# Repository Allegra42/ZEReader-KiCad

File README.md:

<!-- # ZEReader-PCB
ZEReader-PCB is a custom hardware design, intended to be used with the [ZEReader firmware](https://github.com/Allegra42/ZEReader).  
The project is supported by [AISLER](https://aisler.net/en?utm_source=zereader), which sponsor prototying PCBs. See [Production](#production) for more information.  
Thanks [AISLER](https://aisler.net/en?utm_source=zereader)!

- [ZEReader-PCB](#zereader-pcb)
  - [PCB Revisions](#pcb-revisions)
    - [Revision 2](#revision-2)
      - [Known Issues Rev 2](#known-issues-rev-2)
    - [Revision 1](#revision-1)
      - [Known Issues Rev 1](#known-issues-rev-1)
  - [CI and Automation](#ci-and-automation)
  - [Production](#production)
  - [License](#license)

## PCB Revisions
### Revision 2

ZEReader revision 2 is a major redesign of the PCB.
Major improvements and changes in rev 2:
- connected USB-C datalines and added additional ESD and overvoltage protection with USB optimized ESD diodes and a polyfuse
- switched to BQ25170 as a charging controller
- removed the on-PCB NTC for monitoring the lipo temperature in favor for an integrated one
- implemented a new button-based on/off mechanism [based on a self-holding circuit](https://marx.engineer/blog/a-gentle-power-off/)
- fixed FFC connector inversion from rev 1
- removed switch in the display's booster circuit, if you want to use an EPD that needs a 3 ohms resistor populate R11 accordingly
- connect all SD card connector datalines
- reworked and improved general schematic clarity
  - take advantage of the hierarchical sheets
  - use new Pi Pico footprint
  - adopt netclasses in the schematic

#### Known Issues Rev 2
- None, the PCB *is not produced yet*!

### Revision 1
Caution: v1 is working, but the FFC connector is inverted.
Twisting the cable solves the issue for now.
This is to be fixed in the next revision!

#### Known Issues Rev 1
- FFC connector is inverted, twisting the cable is a quick fix
- R11, which defines ISET for the charging controller BQ24092 is too large. 2.7 kohms set a charging current of 200 mA and thus 200 mA for ISET2. In this configuration, the device can not be driven standalone by USB-C. 

## CI and Automation
This project uses GitHub Actions and KiBot for CI/CD.

Outputs can be downloaded in the Actions section. They include:
- BoM (interactive for manual assembly and classical HTML)
- Drill file (.drl)
- Gerber files (.gbr)
- KiRi KiCad Revision Inspector files and server
  To make use of KiRi, move everything besides 'kiri-server' in a subdirectory called 'web'
  and start the server using 'python kiri-server .' from the KiRi directory
- PCB Renderings
- PDF Schematic/PCB printout from KiCad
- ERC Output (HTML)
- DRC Output (HTML)
- Fabrication Ready Zip

All CI generated output files like schematic and pcb should contain the git revision hash
of the commit they were generated from to clearly identify the exact design version.
The git revision hash is also added as a silk screen label to the manufacturing files.

This intended to help with a more agile approach in hardware development.
Besides, KiRi makes it easy to visualize and understand changes in schematic and pcb files tracked by git.

## Production
[AISLER](https://aisler.net/en?utm_source=zereader) supports the ZEReader project with prototyping PCBs. Hugh thank you for that!

To get the lastest git head manufactured, just follow this link for [Uploading to AISLER](https://aisler.net/p/new?url=https://raw.githubusercontent.com/Allegra42/ZEReader-KiCad/refs/heads/main/ZEReader-Pico.kicad_pcb&ref=github).

Alternatively, the GitHub Actions output already contains a prepacked ZIP file with everything needed for production (Gerber files as well as the .kicad_pcb) and correct git revisions filled in.

## License
While the project is license as CERN-OHL-S v2, the squirrel logo is a registered design and not allowed to be used in other contexts. -->

# ZEReader KiCad

The ZEReader PCB is the custom open-hardware board designed for the [ZEReader](https://github.com/Allegra42/ZEReader) project — an open hardware eBook reader approach.

The project is supported by [AISLER](https://aisler.net/en?utm_source=zereader), which sponsors prototype boards. See [Production](#production) for more information.
Huge thanks to [AISLER](https://aisler.net/en?utm_source=zereader) for their support!

---

## Table of Contents

- [ZEReader KiCad](#zereader-kicad)
  - [Table of Contents](#table-of-contents)
  - [PCB Revisions](#pcb-revisions)
    - [Revision 2](#revision-2)
      - [Known Issues Rev 2](#known-issues-rev-2)
    - [Revision 1](#revision-1)
      - [Known Issues Rev 1](#known-issues-rev-1)
  - [CI and Automation](#ci-and-automation)
  - [Production](#production)
    - [Option 1: Tip of the Tree Production](#option-1-tip-of-the-tree-production)
    - [Option 2: Using Pre-Generated Artifacts](#option-2-using-pre-generated-artifacts)
  - [Thanks](#thanks)
  - [License](#license)

---

## PCB Revisions

### Revision 2

**Current Status:** The board is **working**, but USB-C cannot be used for flashing. Use the Micro-USB port on the Raspberry Pi Pico 2 instead!

This revision is a major redesign, focused on fixing Rev 1 issues and significantly improving power handling and robustness.

Major improvements and changes in rev 2:

- Connected **USB-C datalines** and added additional **ESD and overvoltage protection** with USB optimized ESD diodes and a polyfuse.
- Switched to **BQ25170** as a charging controller.
- Removed the on-board NTC for monitoring the LiPo temperature in favor of an integrated one.
- Implemented a new **button-based on/off mechanism** [based on a self-holding circuit](https://marx.engineer/blog/a-gentle-power-off/).
- Fixed **FFC connector inversion** from rev 1.
- Removed switch in the display's booster circuit; populate R11 accordingly for EPDs that require a 3-ohm resistor.
- Connected all SD card connector datalines.
- Switched to a standard SWD pin header format (2x05, 1.27 pitch) for convenience.
- Reworked and improved general schematic clarity (hierarchical sheets, new Pi Pico footprint, netclasses adoption).
- Improved BoM.

#### Known Issues Rev 2

| Issue | Workaround/Impact |
| :--- | :--- |
| **USB-C / Power Path** | **USB-C cannot be used for firmware flashing.** The current power path design gates the entire circuit through the on/off button. Because flashing requires constant power, the controller cuts out during the process unless the button is manually held down (which is unreliable). <br>*Status: To be fixed in the next hardware revision. Use the Raspberry Pi Pico's micro-USB for now!*  |
| **Front-Side Buttons** | Front-side buttons are centered relative to the physical PCB dimensions, rather than the active display area. This results in a visual asymmetry. |

### Revision 1

**Current Status:** The board is **working**, but the FFC connector is inverted.
Twisting the cable solves the issue for now.

#### Known Issues Rev 1

| Issue | Workaround/Impact |
| :--- | :--- |
| **FFC Connector** | **Inverted!** Requires **twisting the FFC cable** before connection. |
| **Charging Circuit**| R11 (ISET for BQ24092) is too large (2.7-kohms). This sets charging current to 200 mA, which is insufficient to drive the device standalone by USB-C. |

---

## CI and Automation

This project uses **GitHub Actions** and **KiBot** for continuous integration and delivery. This ensures that all manufacturing files are up-to-date and directly traceable to the source code.

Outputs can be downloaded in the Actions section. They include:

- **Fabrication Ready Zip**
- Gerber files (.gbr)
- Drill file (.drl)
- Bill of Materials (BoM) (interactive for manual assembly and classical HTML)
- Board Renderings and PDF Schematic/Board printouts
- Verification Reports: ERC Output (HTML), DRC Output (HTML)
- KiRi KiCad Revision Inspector files (for visualizing design changes)

> **Version Control:** All CI-generated output files like schematic and board should contain the **git revision hash** of the commit they were generated from to clearly identify the exact design version. The git revision hash is also added as a silkscreen label to the manufacturing files.

---

## Production

[AISLER](https://aisler.net/en?utm_source=zereader) supports the ZEReader project with prototyping boards. Huge thank you for that!

### Option 1: Tip of the Tree Production

To get the design from the latest commit manufactured, just follow this link for **[Uploading to AISLER](https://aisler.net/p/new?url=https://raw.githubusercontent.com/Allegra42/ZEReader-KiCad/refs/heads/main/ZEReader-Pico.kicad_pcb&ref=github)**.

### Option 2: Using Pre-Generated Artifacts

The GitHub Actions output already contains a **prepacked ZIP file** with everything needed for production (Gerber files as well as the `.kicad_pcb`) and correct git revisions filled in. This is the **best way to order a specific, verified commit version**.  
The generated output is optimized for AISLER. If using a different manufacturing service, please verify that the production files meet their specific requirements.

1.  Navigate to the **GitHub Actions** page for the desired commit.
2.  Download the **`KiBot_Outputs`** artifact.
3.  Upload the Gerber files or the `.kicad_pcb` to [AISLER](https://aisler.net/en?utm_source=zereader).

---
## Thanks
- to [casartar](https://github.com/casartar) for reviewing the design and some great tips and ideas!

## License

While the project is licensed as **CERN Open Hardware Licence Version 2 - Strongly Reciprocal (CERN-OHL-S v2)**, the squirrel logo is a registered design and not allowed to be used in other contexts.

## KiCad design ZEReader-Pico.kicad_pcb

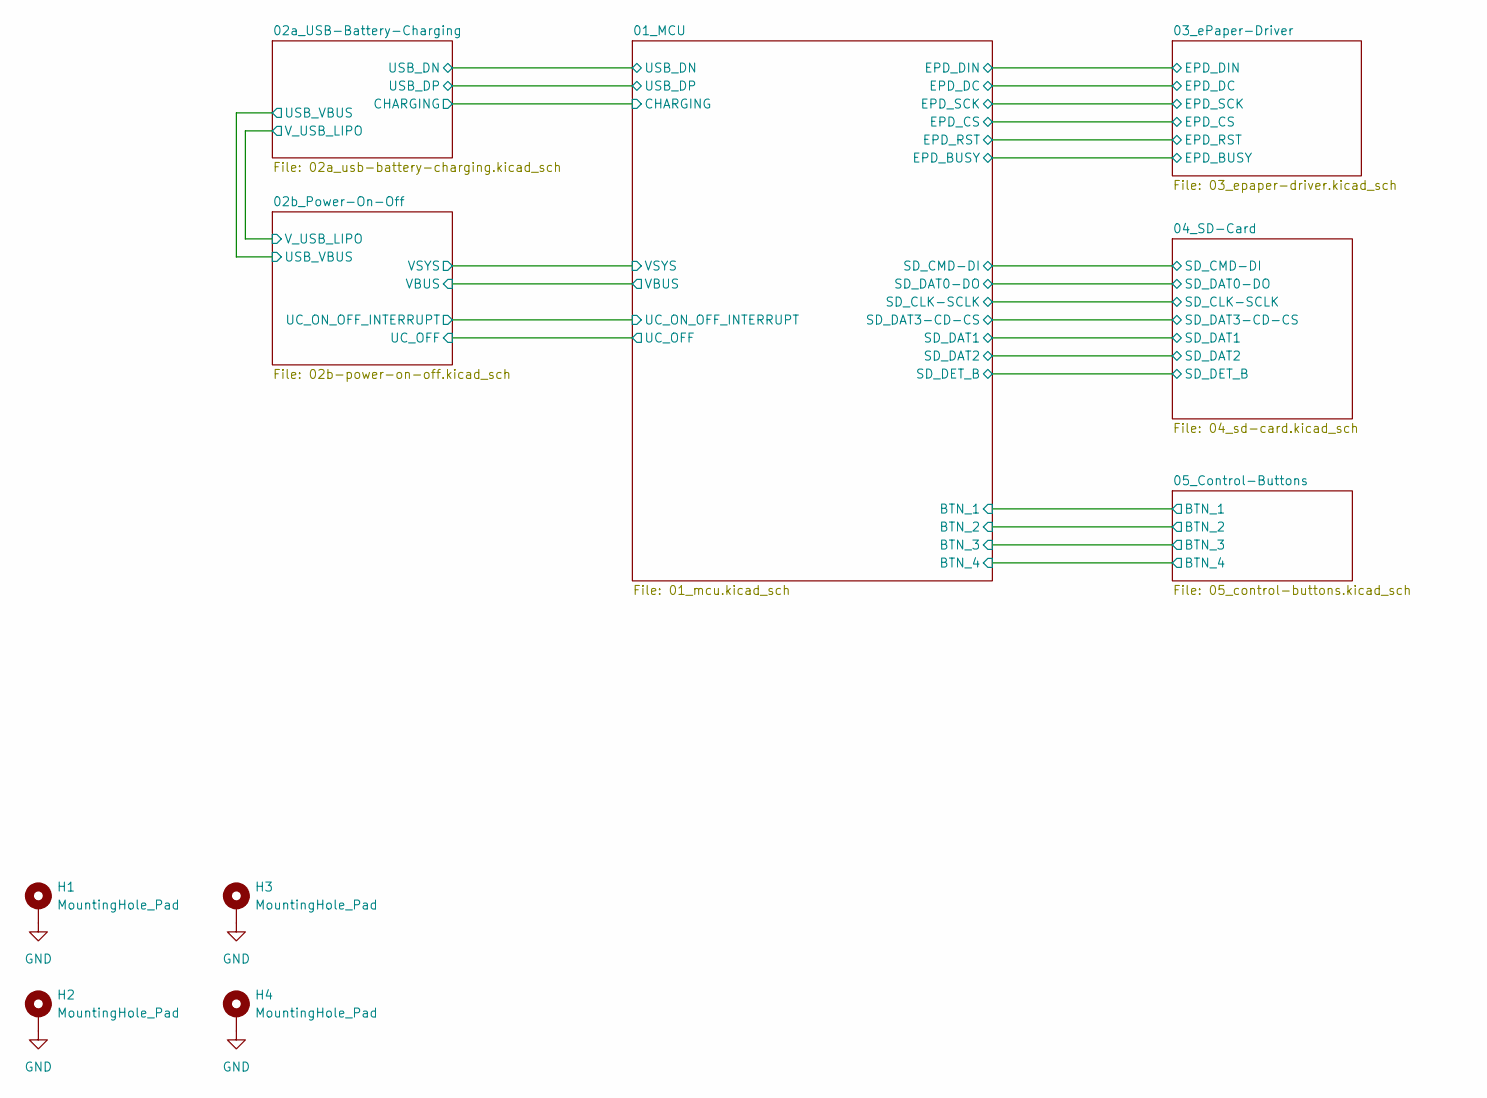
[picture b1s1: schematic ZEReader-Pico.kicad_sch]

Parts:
H1, H2, H3, H4: MountingHole_Pad; MountingHole_3.2mm_M3_Pad_Via

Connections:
GND: H1.1, H2.1, H3.1, H4.1; also elsewhere on the board

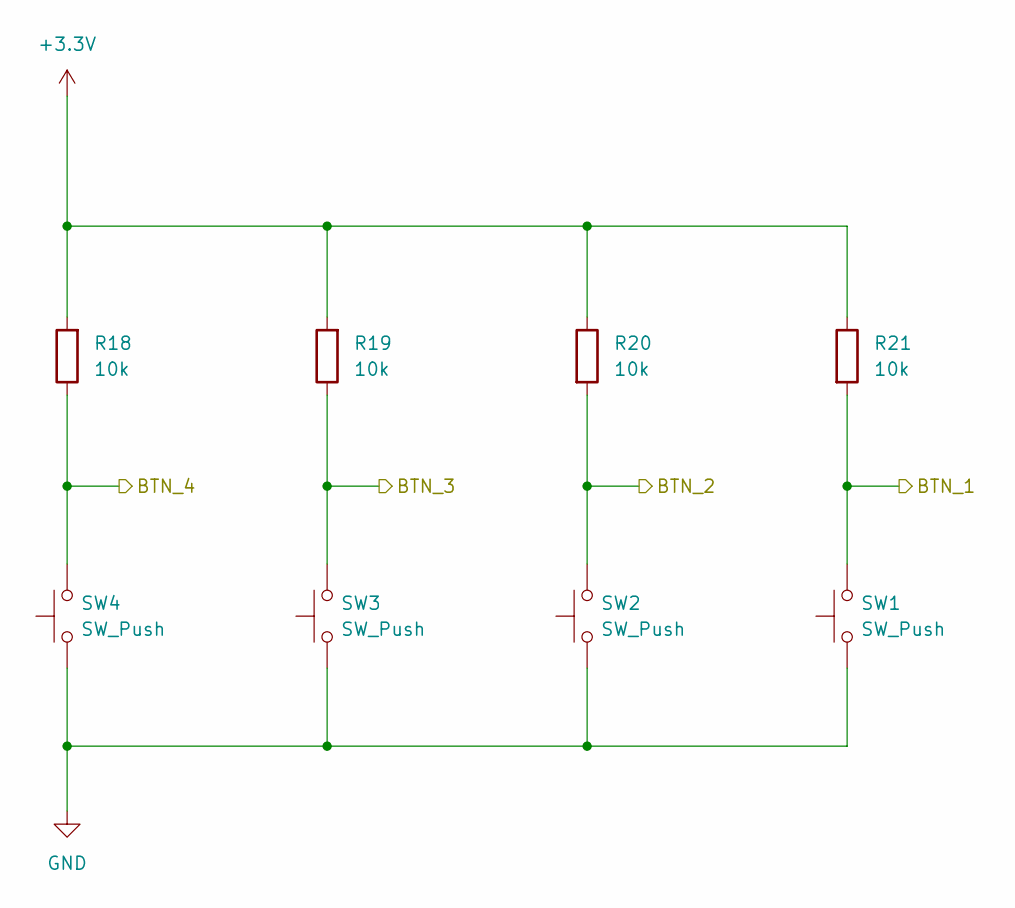
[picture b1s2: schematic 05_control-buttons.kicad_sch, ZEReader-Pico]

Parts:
R18, R19, R20, R21: 10k; R_1206_3216Metric_Pad1.30x1.75mm_HandSolder; Manufacturer PartNo RC1206FR-0710KL; DigiKey 311-10.0KFRCT-ND
SW1, SW2, SW3, SW4: SW_Push; SW_PUSH_6mm; Manufacturer PartNo 1825910-6; DigiKey 450-1650-ND

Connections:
+3.3V: R18.2, R19.2, R20.1, R21.1; also elsewhere on the board
/01_MCU/BTN_1: R21.2, SW1.2; also elsewhere on the board
/01_MCU/BTN_2: R20.2, SW2.2; also elsewhere on the board
/01_MCU/BTN_3: R19.1, SW3.2; also elsewhere on the board
/01_MCU/BTN_4: R18.1, SW4.2; also elsewhere on the board
GND: SW1.1, SW2.1, SW3.1, SW4.1; also elsewhere on the board

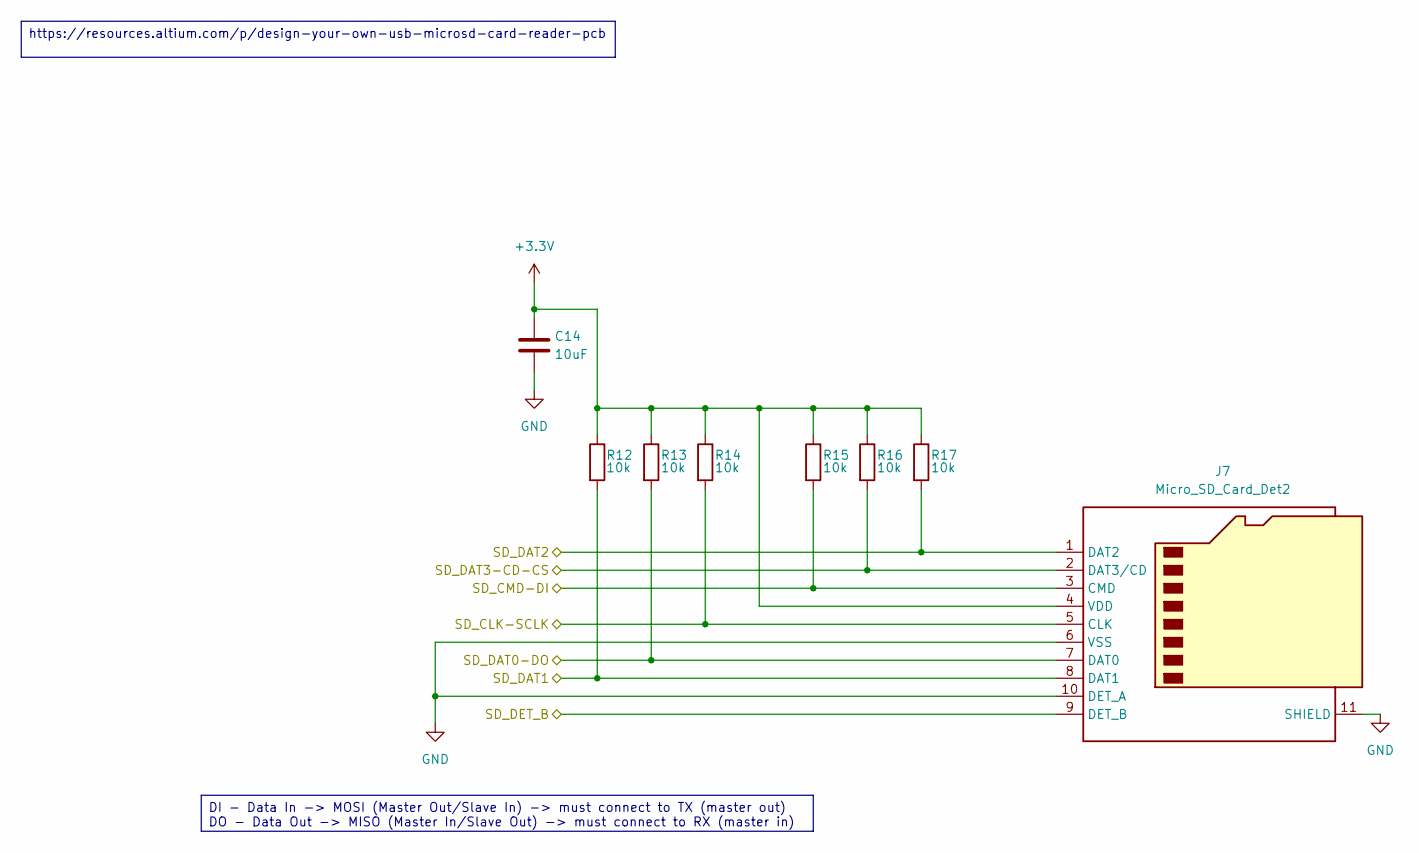
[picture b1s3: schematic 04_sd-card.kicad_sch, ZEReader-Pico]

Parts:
C14: 10uF; C_1206_3216Metric_Pad1.33x1.80mm_HandSolder; Manufacturer PartNo CL31B106KAHNNNE; DigiKey 1276-1804-1-ND
J7: Micro_SD_Card_Det2; microSD_HC_Hirose_DM3AT-SF-PEJM5; Manufacturer PartNo DM3AT-SF-PEJM5; DigiKey HR1964CT-ND
R12, R13, R14, R15, R16, R17: 10k; R_1206_3216Metric_Pad1.30x1.75mm_HandSolder; Manufacturer PartNo RC1206FR-0710KL; DigiKey 311-10.0KFRCT-ND

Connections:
+3.3V: C14.1, J7.4 (VDD), R12.1, R13.1, R14.1, R15.1, R16.1, R17.1; also elsewhere on the board
/01_MCU/SD_CLK-SCLK: J7.5 (CLK), R14.2; also elsewhere on the board
/01_MCU/SD_CMD-DI: J7.3 (CMD), R15.2; also elsewhere on the board
/01_MCU/SD_DAT0-DO: J7.7 (DAT0), R13.2; also elsewhere on the board
/01_MCU/SD_DAT1: J7.8 (DAT1), R12.2; also elsewhere on the board
/01_MCU/SD_DAT2: J7.1 (DAT2), R17.2; also elsewhere on the board
/01_MCU/SD_DAT3-CD-CS: J7.2 (DAT3/CD), R16.2; also elsewhere on the board
/01_MCU/SD_DET_B: J7.9 (DET_B); also elsewhere on the board
GND: C14.2, J7.6 (VSS), J7.10 (DET_A), J7.11 (SHIELD); also elsewhere on the board

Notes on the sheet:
DI - Data In -> MOSI (Master Out/Slave In) -> must connect to TX (master out) DO - Data Out -> MISO (Master In/Slave Out) -> must connect to RX (master in)
https://resources.altium.com/p/design-your-own-usb-microsd-card-reader-pcb

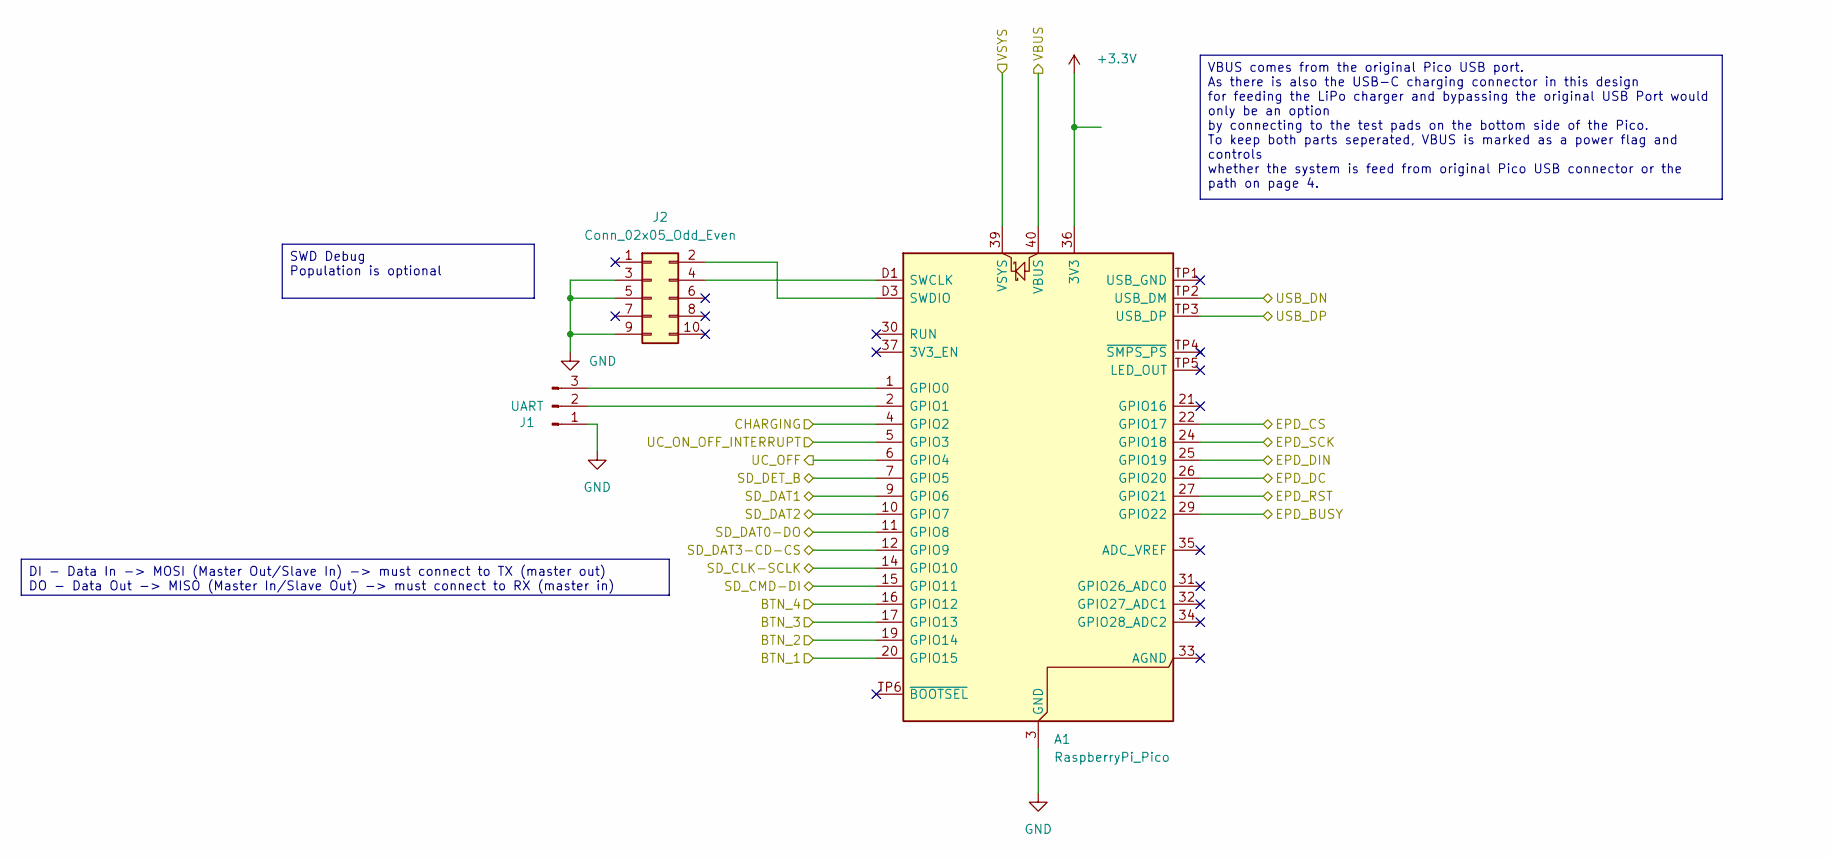
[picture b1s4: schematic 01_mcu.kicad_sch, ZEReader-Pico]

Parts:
A1: RaspberryPi_Pico; RaspberryPi_Pico_SMD; Manufacturer PartNo SC1631; DigiKey 2648-SC1631CT-ND
J1: UART; PinHeader_1x03_P2.54mm_Vertical; Manufacturer PartNo G800W305018EU; DigiKey 664-G800W305018EU-ND
J2: Conn_02x05_Odd_Even; PinHeader_2x05_P1.27mm_Vertical_SMD; Manufacturer PartNo BD125-10-A-0305-0580-L-B; DigiKey 2073-BD125-10-A-0305-0580-L-BCT-ND

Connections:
+3.3V: A1.36 (3V3); also elsewhere on the board
/01_MCU/BTN_1: A1.20 (GPIO15); also elsewhere on the board
/01_MCU/BTN_2: A1.19 (GPIO14); also elsewhere on the board
/01_MCU/BTN_3: A1.17 (GPIO13); also elsewhere on the board
/01_MCU/BTN_4: A1.16 (GPIO12); also elsewhere on the board
/01_MCU/CHARGING: A1.4 (GPIO2); also elsewhere on the board
/01_MCU/EPD_BUSY: A1.29 (GPIO22); also elsewhere on the board
/01_MCU/EPD_CS: A1.22 (GPIO17); also elsewhere on the board
/01_MCU/EPD_DC: A1.26 (GPIO20); also elsewhere on the board
/01_MCU/EPD_DIN: A1.25 (GPIO19); also elsewhere on the board
/01_MCU/EPD_RST: A1.27 (GPIO21); also elsewhere on the board
/01_MCU/EPD_SCK: A1.24 (GPIO18); also elsewhere on the board
/01_MCU/SD_CLK-SCLK: A1.14 (GPIO10); also elsewhere on the board
/01_MCU/SD_CMD-DI: A1.15 (GPIO11); also elsewhere on the board
/01_MCU/SD_DAT0-DO: A1.11 (GPIO8); also elsewhere on the board
/01_MCU/SD_DAT1: A1.9 (GPIO6); also elsewhere on the board
/01_MCU/SD_DAT2: A1.10 (GPIO7); also elsewhere on the board
/01_MCU/SD_DAT3-CD-CS: A1.12 (GPIO9); also elsewhere on the board
/01_MCU/SD_DET_B: A1.7 (GPIO5); also elsewhere on the board
/01_MCU/UC_OFF: A1.6 (GPIO4); also elsewhere on the board
/01_MCU/UC_ON_OFF_INTERRUPT: A1.5 (GPIO3); also elsewhere on the board
/01_MCU/USB_DN: A1.TP2 (USB_DM); also elsewhere on the board
/01_MCU/USB_DP: A1.TP3 (USB_DP); also elsewhere on the board
/01_MCU/VBUS: A1.40 (VBUS); also elsewhere on the board
/01_MCU/VSYS: A1.39 (VSYS); also elsewhere on the board
GND: A1.3 (GND), A1.8 (GND), A1.13 (GND), A1.18 (GND), A1.23 (GND), A1.28 (GND), A1.38 (GND), A1.D2 (GND), J1.1, J2.3, J2.5, J2.9; also elsewhere on the board
unnamed: A1.1 (GPIO0), J1.3
unnamed: A1.2 (GPIO1), J1.2
unnamed: A1.D1 (SWCLK), J2.4
unnamed: A1.D3 (SWDIO), J2.2

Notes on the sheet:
VBUS comes from the original Pico USB port. As there is also the USB-C charging connector in this design for feeding the LiPo charger and bypassing the original USB Port would only be an option by connecting to the test pads on the bottom side of the Pico. To keep both parts seperated, VBUS is mark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
DI - Data In -> MOSI (Master Out/Slave In) -> must connect to TX (master out) DO - Data Out -> MISO (Master In/Slave Out) -> must connect to RX (master in)
SWD Debug Population is optional

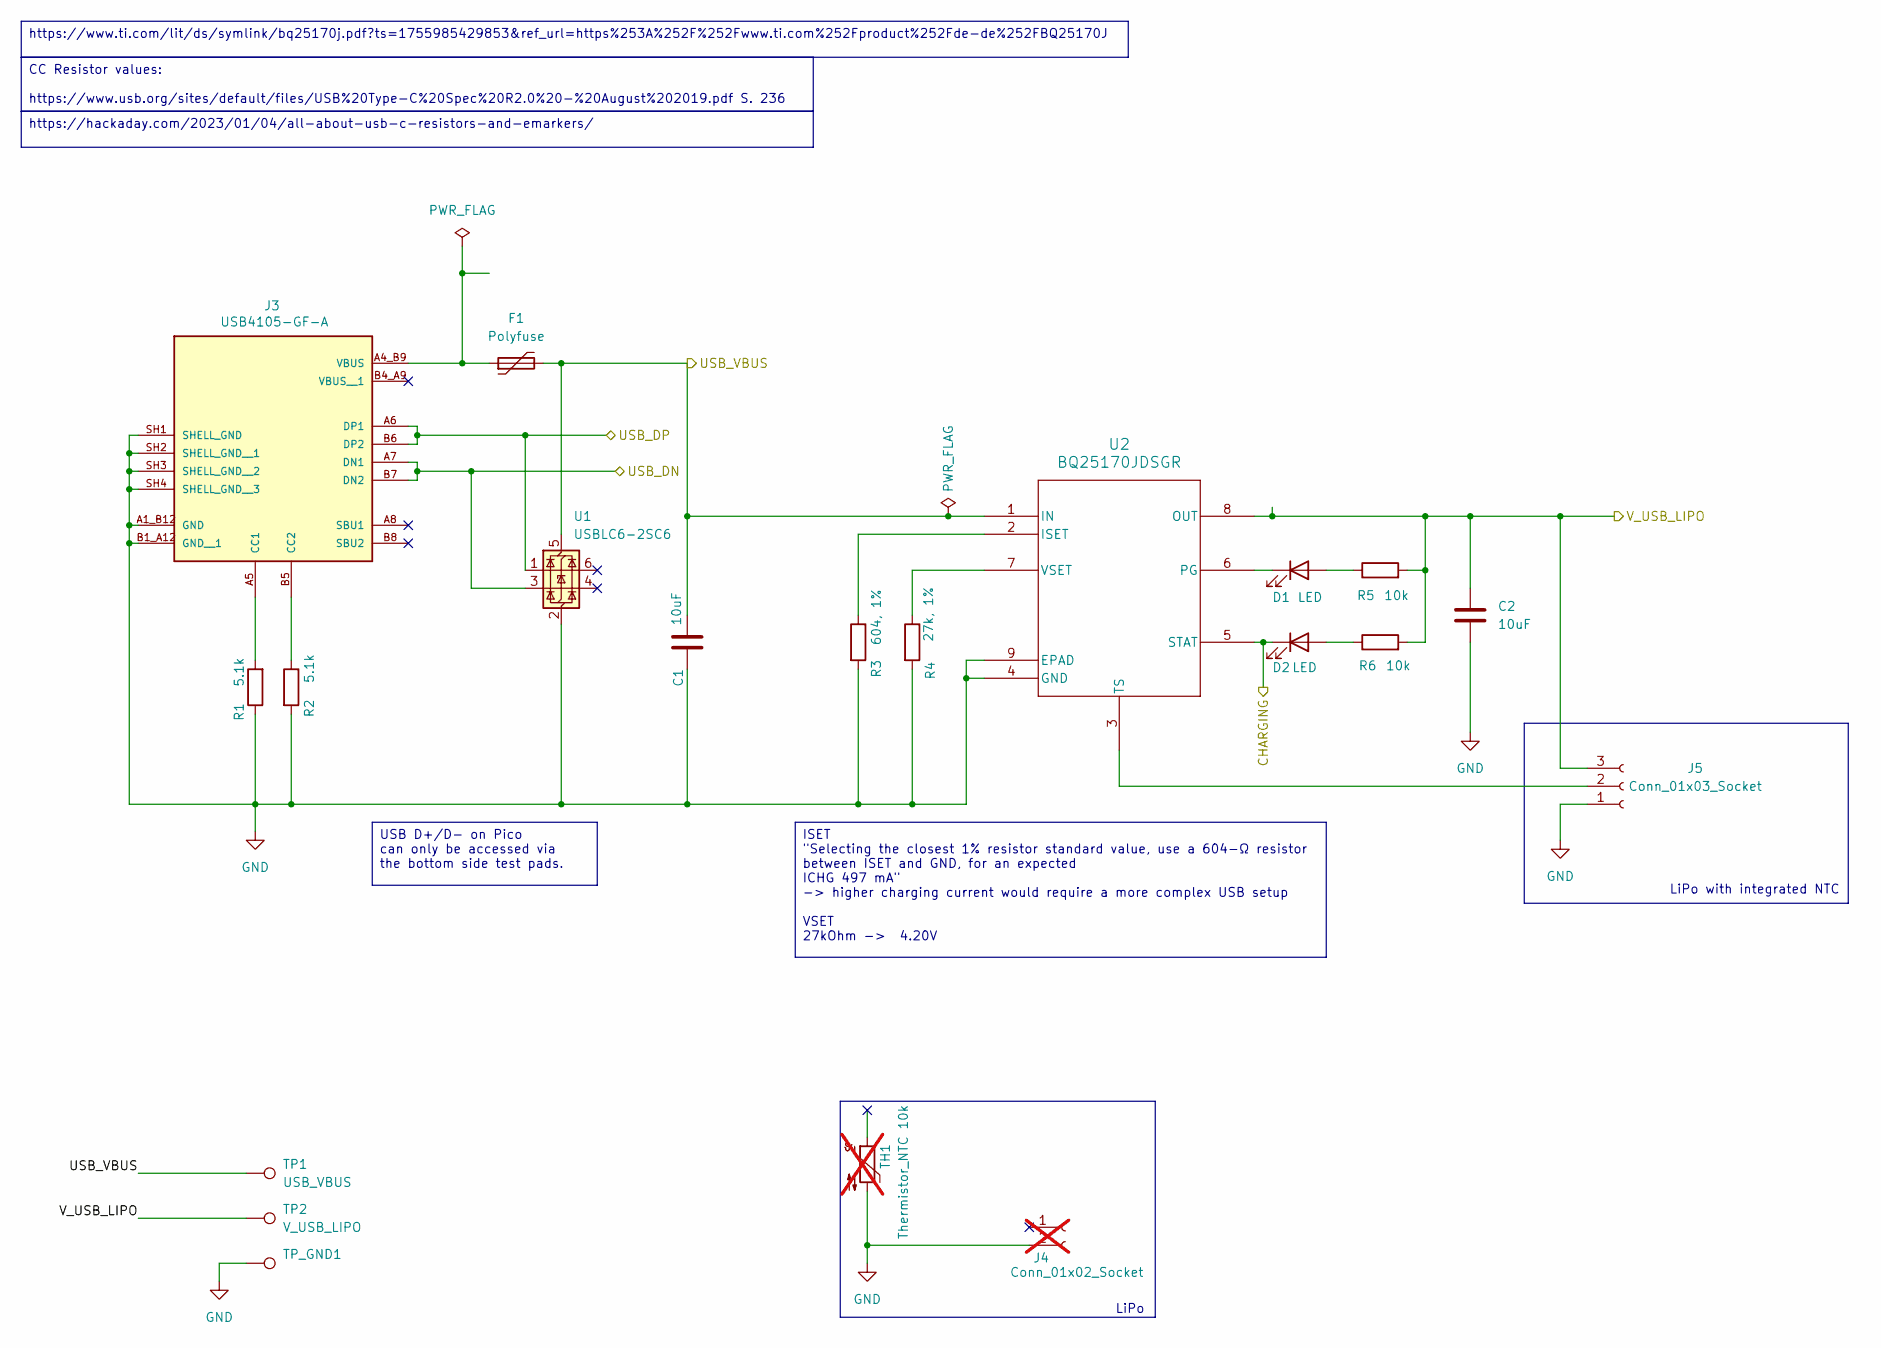
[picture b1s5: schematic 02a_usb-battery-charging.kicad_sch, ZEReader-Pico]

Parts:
C1, C2: 10uF; C_1206_3216Metric_Pad1.33x1.80mm_HandSolder; Manufacturer PartNo CL31B106KAHNNNE; DigiKey 1276-1804-1-ND
D1: LED; LED_1206_3216Metric_Pad1.42x1.75mm_HandSolder; Manufacturer PartNo 150120YS75000; DigiKey 732-4994-1-ND
D2: LED; LED_1206_3216Metric_Pad1.42x1.75mm_HandSolder; Manufacturer PartNo 150120GS75000; DigiKey 732-4990-1-ND
F1: Polyfuse; R_1206_3216Metric_Pad1.30x1.75mm_HandSolder; Manufacturer PartNo 1206L050/15YR; DigiKey F3733CT-ND
J3: USB4105-GF-A; GCT_USB4105-GF-A; PARTREV B4; DigiKey 2073-USB4105-GF-ACT-ND
J4: Conn_01x02_Socket; JST_PH_S2B-PH-K_1x02_P2.00mm_Horizontal; not fitted
J5: Conn_01x03_Socket; JST_PH_S3B-PH-K_1x03_P2.00mm_Horizontal; Manufacturer PartNo S3B-PH-K-S; DigiKey 455-1720-ND
R1, R2: 5.1k; R_1206_3216Metric_Pad1.30x1.75mm_HandSolder; Manufacturer PartNo AC1206FR-075K1L; DigiKey YAG3894CT-ND
R3: 604, 1%; R_1206_3216Metric_Pad1.30x1.75mm_HandSolder; Manufacturer PartNo RNCP1206FTD604R; DigiKey RNCP1206FTD604RCT-ND
R4: 27k, 1%; R_1206_3216Metric_Pad1.30x1.75mm_HandSolder; Manufacturer PartNo RC1206FR-0727KL; DigiKey 311-27.0KFRCT-ND
R5, R6: 10k; R_1206_3216Metric_Pad1.30x1.75mm_HandSolder; Manufacturer PartNo RC1206FR-0710KL; DigiKey 311-10.0KFRCT-ND
TH1: Thermistor_NTC 10k; R_1206_3216Metric_Pad1.30x1.75mm_HandSolder; not fitted
TP1: USB_VBUS; TestPoint_Pad_D2.5mm
TP2: V_USB_LIPO; TestPoint_Pad_D2.5mm
TP_GND1: TestPoint_Pad_D2.5mm
U1: USBLC6-2SC6; SOT-23-6; Manufacturer PartNo USBLC6-2SC6; DigiKey 497-5235-1-ND
U2: BQ25170JDSGR; WSON8_BQ2517_TEX; Manufacturer PartNo BQ25170JDSGR; DigiKey 296-BQ25170JDSGRCT-ND

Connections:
/01_MCU/CHARGING: D2.1 (K), U2.5 (STAT); also elsewhere on the board
/01_MCU/USB_DN: J3.A7 (DN1), J3.B7 (DN2), U1.3 (I/O2); also elsewhere on the board
/01_MCU/USB_DP: J3.A6 (DP1), J3.B6 (DP2), U1.1 (I/O1); also elsewhere on the board
/02a_USB-Battery-Charging/USB_VBUS: C1.1, F1.2, TP1.1, U1.5 (VBUS), U2.1 (IN); also elsewhere on the board
/02a_USB-Battery-Charging/V_USB_LIPO: C2.1, J5.3, R5.2, R6.2, TP2.1, U2.8 (OUT); also elsewhere on the board
GND: C1.2, C2.2, J3.A1_B12 (GND), J3.B1_A12 (GND__1), J3.SH1 (SHELL_GND), J3.SH2 (SHELL_GND__1), J3.SH3 (SHELL_GND__2), J3.SH4 (SHELL_GND__3), J4.2, J5.1, R1.1, R2.2, R3.2, R4.2, TH1.2, TP_GND1.1, U1.2 (GND), U2.4 (GND), U2.9 (EPAD); also elsewhere on the board
unnamed: D1.2 (A), R5.1
unnamed: D1.1 (K), U2.6 (PG)
unnamed: D2.2 (A), R6.1
unnamed: J3.A5 (CC1), R1.2
unnamed: J3.B5 (CC2), R2.1
unnamed: F1.1, J3.A4_B9 (VBUS)
unnamed: J5.2, U2.3 (TS)
unnamed: R3.1, U2.2 (ISET)
unnamed: R4.1, U2.7 (VSET)

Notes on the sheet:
LiPo
LiPo with integrated NTC
CC Resistor values: https://www.usb.org/sites/default/files/USB%20Type-C%20Spec%20R2.0%20-%20August%202019.pdf S. 236
ISET "Selecting the closest 1% resistor standard value, use a 604-Ω resistor between ISET and GND, for an expected ICHG 497 mA" -> higher charging current would require a more complex USB setup VSET 27kOhm -> 4.20V
https://www.ti.com/lit/ds/symlink/bq25170j.pdf?ts=1755985429853&ref_url=https%253A%252F%252Fwww.ti.com%252Fproduct%252Fde-de%252FBQ25170J
https://hackaday.com/2023/01/04/all-about-usb-c-resistors-and-emarkers/
USB D+/D- on Pico can only be accessed via the bottom side test pads.

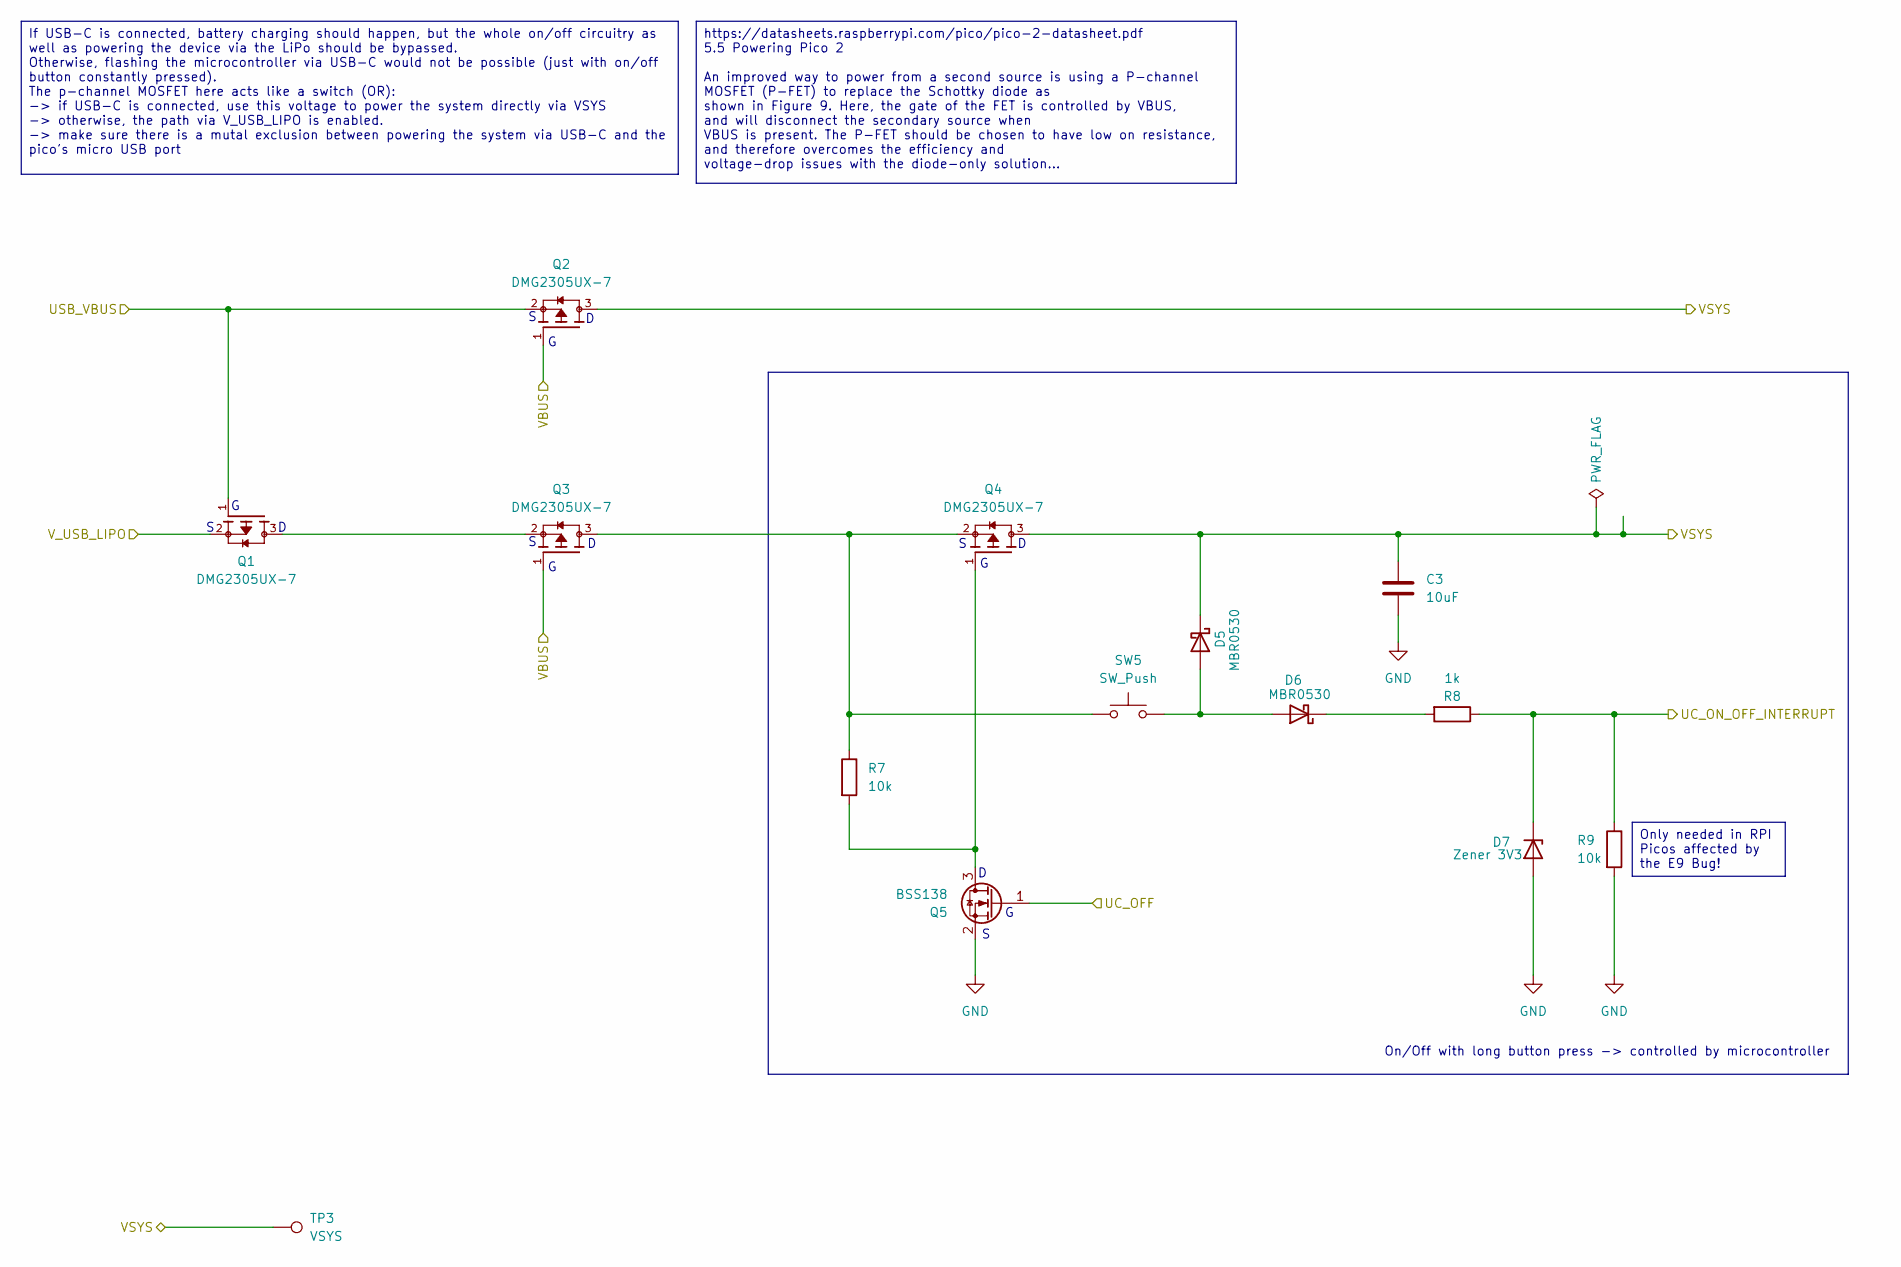
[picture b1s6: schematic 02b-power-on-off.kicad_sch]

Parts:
C3: 10uF; C_1206_3216Metric_Pad1.33x1.80mm_HandSolder; Manufacturer PartNo CL31B106KAHNNNE; DigiKey 1276-1804-1-ND
D5, D6: MBR0530; D_SOD-123; Manufacturer PartNo MBR0530T1G; DigiKey MBR0530T1GOSCT-ND
D7: Zener 3V3; DIO_TDZVT_ROM; Manufacturer PartNo TFZVTR3.3B; DigiKey TFZVTR3.3BCT-ND
Q1, Q2, Q3, Q4: DMG2305UX-7; SOT-23-3; PARTREV 09/2018; DigiKey DMG2305UX-7DICT-ND
Q5: BSS138; SOT-23; Manufacturer PartNo BSS138LT3G; DigiKey BSS138LT3GOSCT-ND
R7, R9: 10k; R_1206_3216Metric_Pad1.30x1.75mm_HandSolder; Manufacturer PartNo RC1206FR-0710KL; DigiKey 311-10.0KFRCT-ND
R8: 1k; R_1206_3216Metric_Pad1.30x1.75mm_HandSolder; Manufacturer PartNo RNCP1206FTD1K00; DigiKey RNCP1206FTD1K00CT-ND
SW5: SW_Push; SW_Push_1P1T_NO_E-Switch_TL3301NxxxxxG; Manufacturer PartNo TL3301NF100QG; DigiKey EG6054CT-ND
TP3: VSYS; TestPoint_Pad_D2.5mm

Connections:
/01_MCU/UC_OFF: Q5.1 (G); also elsewhere on the board
/01_MCU/UC_ON_OFF_INTERRUPT: D7.1 (K), R8.1, R9.1; also elsewhere on the board
/01_MCU/VBUS: Q2.1, Q3.1; also elsewhere on the board
/01_MCU/VSYS: C3.1, D5.1 (K), Q2.3, Q4.3, TP3.1; also elsewhere on the board
/02a_USB-Battery-Charging/USB_VBUS: Q1.1, Q2.2; also elsewhere on the board
/02a_USB-Battery-Charging/V_USB_LIPO: Q1.2; also elsewhere on the board
GND: C3.2, D7.2 (A), Q5.2 (S), R9.2; also elsewhere on the board
unnamed: D5.2 (A), D6.2 (A), SW5.2
unnamed: D6.1 (K), R8.2
unnamed: Q1.3, Q3.2
unnamed: Q3.3, Q4.2, R7.1, SW5.1
unnamed: Q4.1, Q5.3 (D), R7.2

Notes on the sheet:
On/Off with long button press -> controlled by microcontroller
If USB-C is connected, battery charging should happen, but the whole on/off circuitry as well as powering the device via the LiPo should be bypassed. Otherwise, flashing the microcontroller via USB-C would not be possible (just with on/off button constantly pressed). The p-channel MOSFET here acts 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
https://datasheets.raspberrypi.com/pico/pico-2-datasheet.pdf 5.5 Powering Pico 2 An improved way to power from a second source is using a P-channel MOSFET (P-FET) to replace the Schottky diode as shown in Figure 9. Here, the gate of the FET is controlled by VBUS, and will disconnect the secondary s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
Only needed in RPI Picos affected by the E9 Bug!

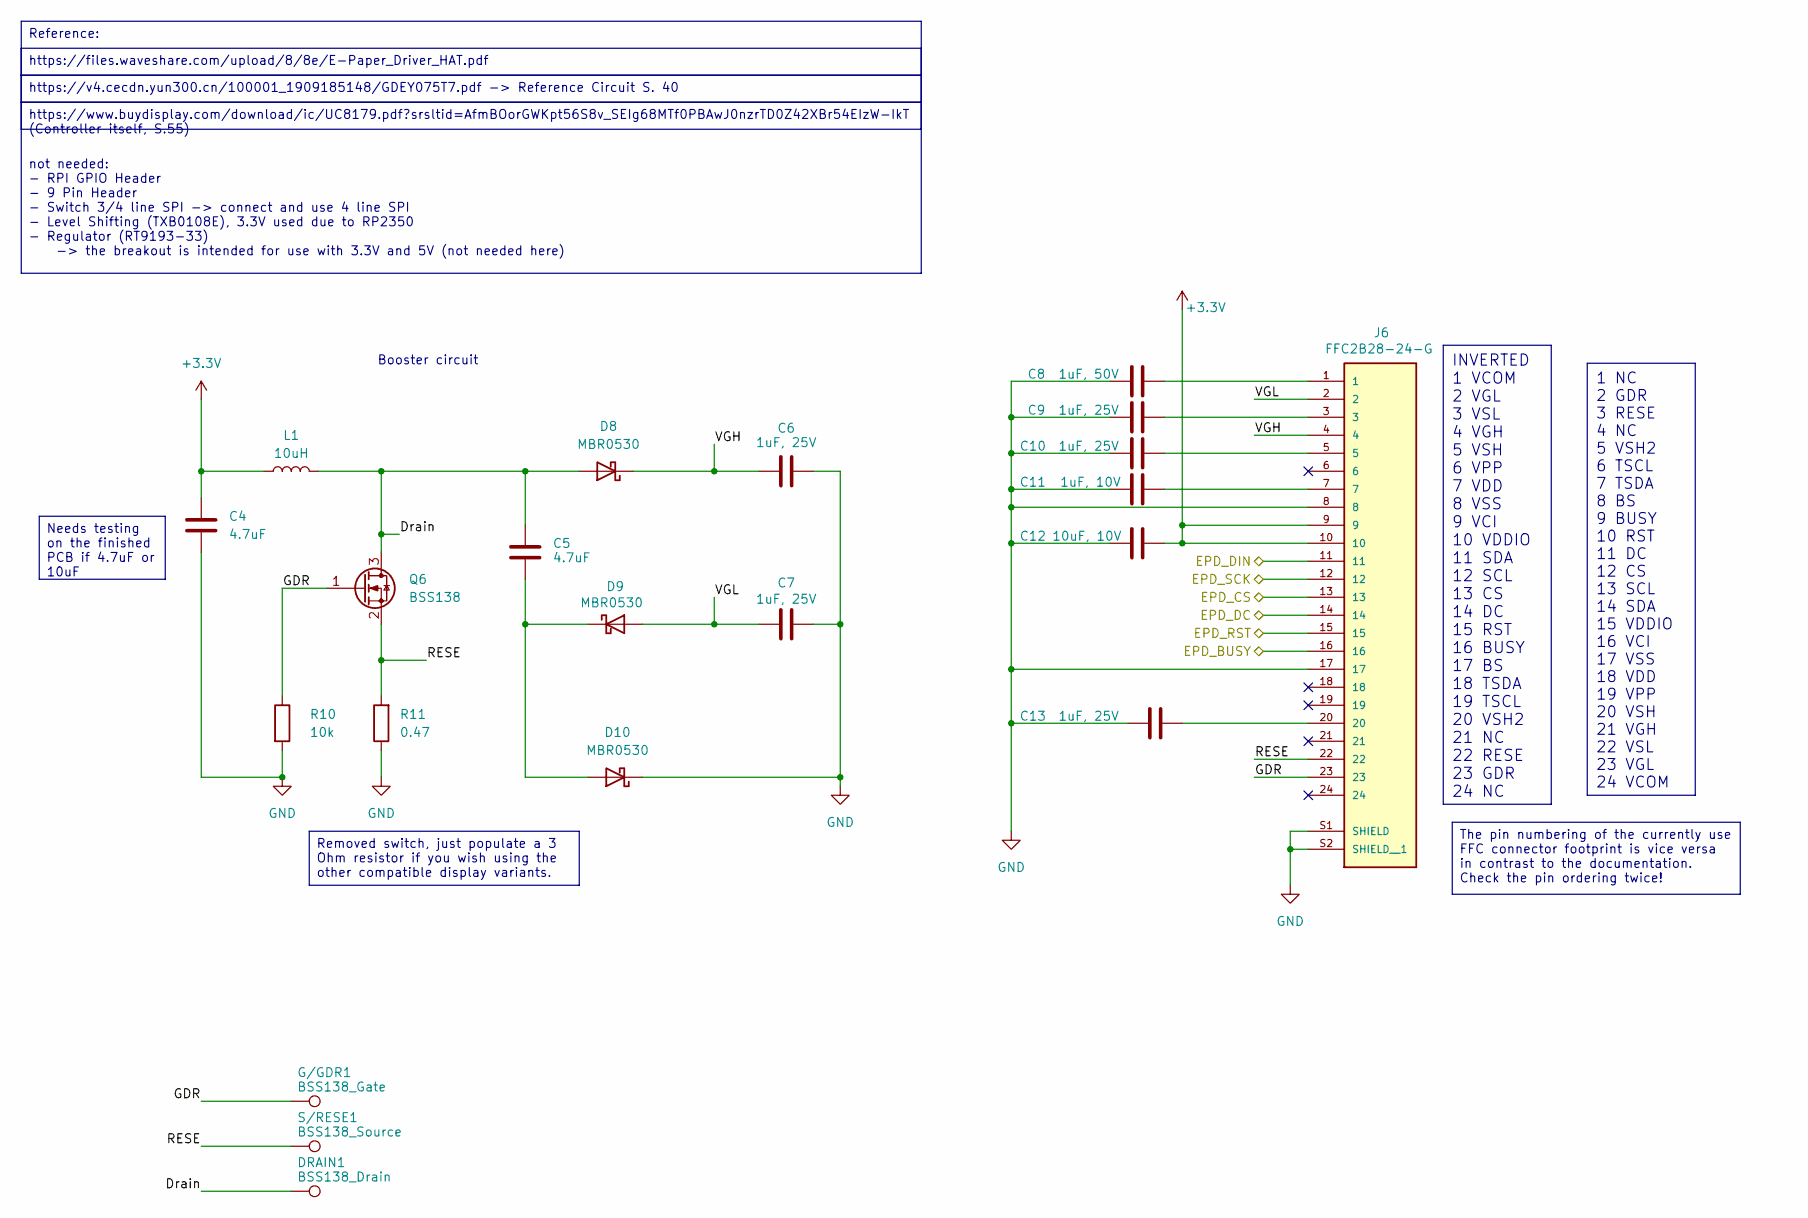
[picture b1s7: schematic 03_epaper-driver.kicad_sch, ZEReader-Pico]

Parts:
C4, C5: 4.7uF; C_1206_3216Metric_Pad1.33x1.80mm_HandSolder; Manufacturer PartNo CL31B475KBHNFNE; DigiKey 1276-3179-1-ND
C6, C7, C9, C10, C13: 1uF, 25V; C_1206_3216Metric_Pad1.33x1.80mm_HandSolder; Manufacturer PartNo CL31B105KBHNFNE; DigiKey 1276-3091-1-ND
C8: 1uF, 50V; C_1206_3216Metric_Pad1.33x1.80mm_HandSolder; Manufacturer PartNo CL31B105KBHNFNE; DigiKey 1276-3091-1-ND
C11: 1uF, 10V; C_1206_3216Metric_Pad1.33x1.80mm_HandSolder; Manufacturer PartNo CL31B105KBHNFNE; DigiKey 1276-3091-1-ND
C12: 10uF, 10V; C_1206_3216Metric_Pad1.33x1.80mm_HandSolder; Manufacturer PartNo CL31B106KAHNNNE; DigiKey 1276-1804-1-ND
D8, D9, D10: MBR0530; D_SOD-123; Manufacturer PartNo MBR0530T1G; DigiKey MBR0530T1GOSCT-ND
DRAIN1: BSS138_Drain; TestPoint_Pad_D2.5mm
G/GDR1: BSS138_Gate; TestPoint_Pad_D2.5mm
J6: FFC2B28-24-G; GCT_FFC2B28-24-G; PARTREV A; DigiKey 2073-FFC2B28-24-GCT-ND
L1: 10uH; IND_IFSC_1515AH_VIS-L; Manufacturer PartNo IFSC1515AHER100M01; DigiKey 541-1406-1-ND
Q6: BSS138; SOT-23; Manufacturer PartNo BSS138LT3G; DigiKey BSS138LT3GOSCT-ND
R10: 10k; R_1206_3216Metric_Pad1.30x1.75mm_HandSolder; Manufacturer PartNo RC1206FR-0710KL; DigiKey 311-10.0KFRCT-ND
R11: 0.47; R_1206_3216Metric_Pad1.30x1.75mm_HandSolder; Manufacturer PartNo KDV12DR470ET; DigiKey 273-KDV12DR470ETCT-ND
S/RESE1: BSS138_Source; TestPoint_Pad_D2.5mm

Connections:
+3.3V: C4.1, C12.2, J6.9, J6.10, L1.1; also elsewhere on the board
/01_MCU/EPD_BUSY: J6.16; also elsewhere on the board
/01_MCU/EPD_CS: J6.13; also elsewhere on the board
/01_MCU/EPD_DC: J6.14; also elsewhere on the board
/01_MCU/EPD_DIN: J6.11; also elsewhere on the board
/01_MCU/EPD_RST: J6.15; also elsewhere on the board
/01_MCU/EPD_SCK: J6.12; also elsewhere on the board
/03_ePaper-Driver/Drain: C5.1, D8.2 (A), DRAIN1.1, L1.2, Q6.3 (D)
/03_ePaper-Driver/GDR: G/GDR1.1, J6.23, Q6.1 (G), R10.1
/03_ePaper-Driver/RESE: J6.22, Q6.2 (S), R11.2, S/RESE1.1
/03_ePaper-Driver/VGH: C6.1, D8.1 (K), J6.4
/03_ePaper-Driver/VGL: C7.1, D9.2 (A), J6.2
GND: C4.2, C6.2, C7.2, C8.1, C9.1, C10.1, C11.1, C12.1, C13.1, D10.1 (K), J6.8, J6.17, J6.S1 (SHIELD), J6.S2 (SHIELD__1), R10.2, R11.1; also elsewhere on the board
unnamed: C8.2, J6.1
unnamed: C9.2, J6.3
unnamed: C10.2, J6.5
unnamed: C11.2, J6.7
unnamed: C13.2, J6.20
unnamed: C5.2, D9.1 (K), D10.2 (A)

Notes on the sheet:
Booster circuit
https://files.waveshare.com/upload/8/8e/E-Paper_Driver_HAT.pdf
INVERTED 1 VCOM 2 VGL 3 VSL 4 VGH 5 VSH 6 VPP 7 VDD 8 VSS 9 VCI 10 VDDIO 11 SDA 12 SCL 13 CS 14 DC 15 RST 16 BUSY 17 BS 18 TSDA 19 TSCL 20 VSH2 21 NC 22 RESE 23 GDR 24 NC
https://v4.cecdn.yun300.cn/100001_1909185148/GDEY075T7.pdf -> Reference Circuit S. 40
Needs testing on the finished PCB if 4.7uF or 10uF
https://www.buydisplay.com/download/ic/UC8179.pdf?srsltid=AfmBOorGWKpt56S8v_SEIg68MTf0PBAwJ0nzrTD0Z42XBr54EIzW-IkT (Controller itself, S.55)
Removed switch, just populate a 3 Ohm resistor if you wish using the other compatible display variants.
The pin numbering of the currently use FFC connector footprint is vice versa in contrast to the documentation. Check the pin ordering twice!
1 NC 2 GDR 3 RESE 4 NC 5 VSH2 6 TSCL 7 TSDA 8 BS 9 BUSY 10 RST 11 DC 12 CS 13 SCL 14 SDA 15 VDDIO 16 VCI 17 VSS 18 VDD 19 VPP 20 VSH 21 VGH 22 VSL 23 VGL 24 VCOM
Reference: not needed: - RPI GPIO Header - 9 Pin Header - Switch 3/4 line SPI -> connect and use 4 line SPI - Level Shifting (TXB0108E), 3.3V used due to RP2350 - Regulator (RT9193-33) -> the breakout is intended for use with 3.3V and 5V (not needed here)
